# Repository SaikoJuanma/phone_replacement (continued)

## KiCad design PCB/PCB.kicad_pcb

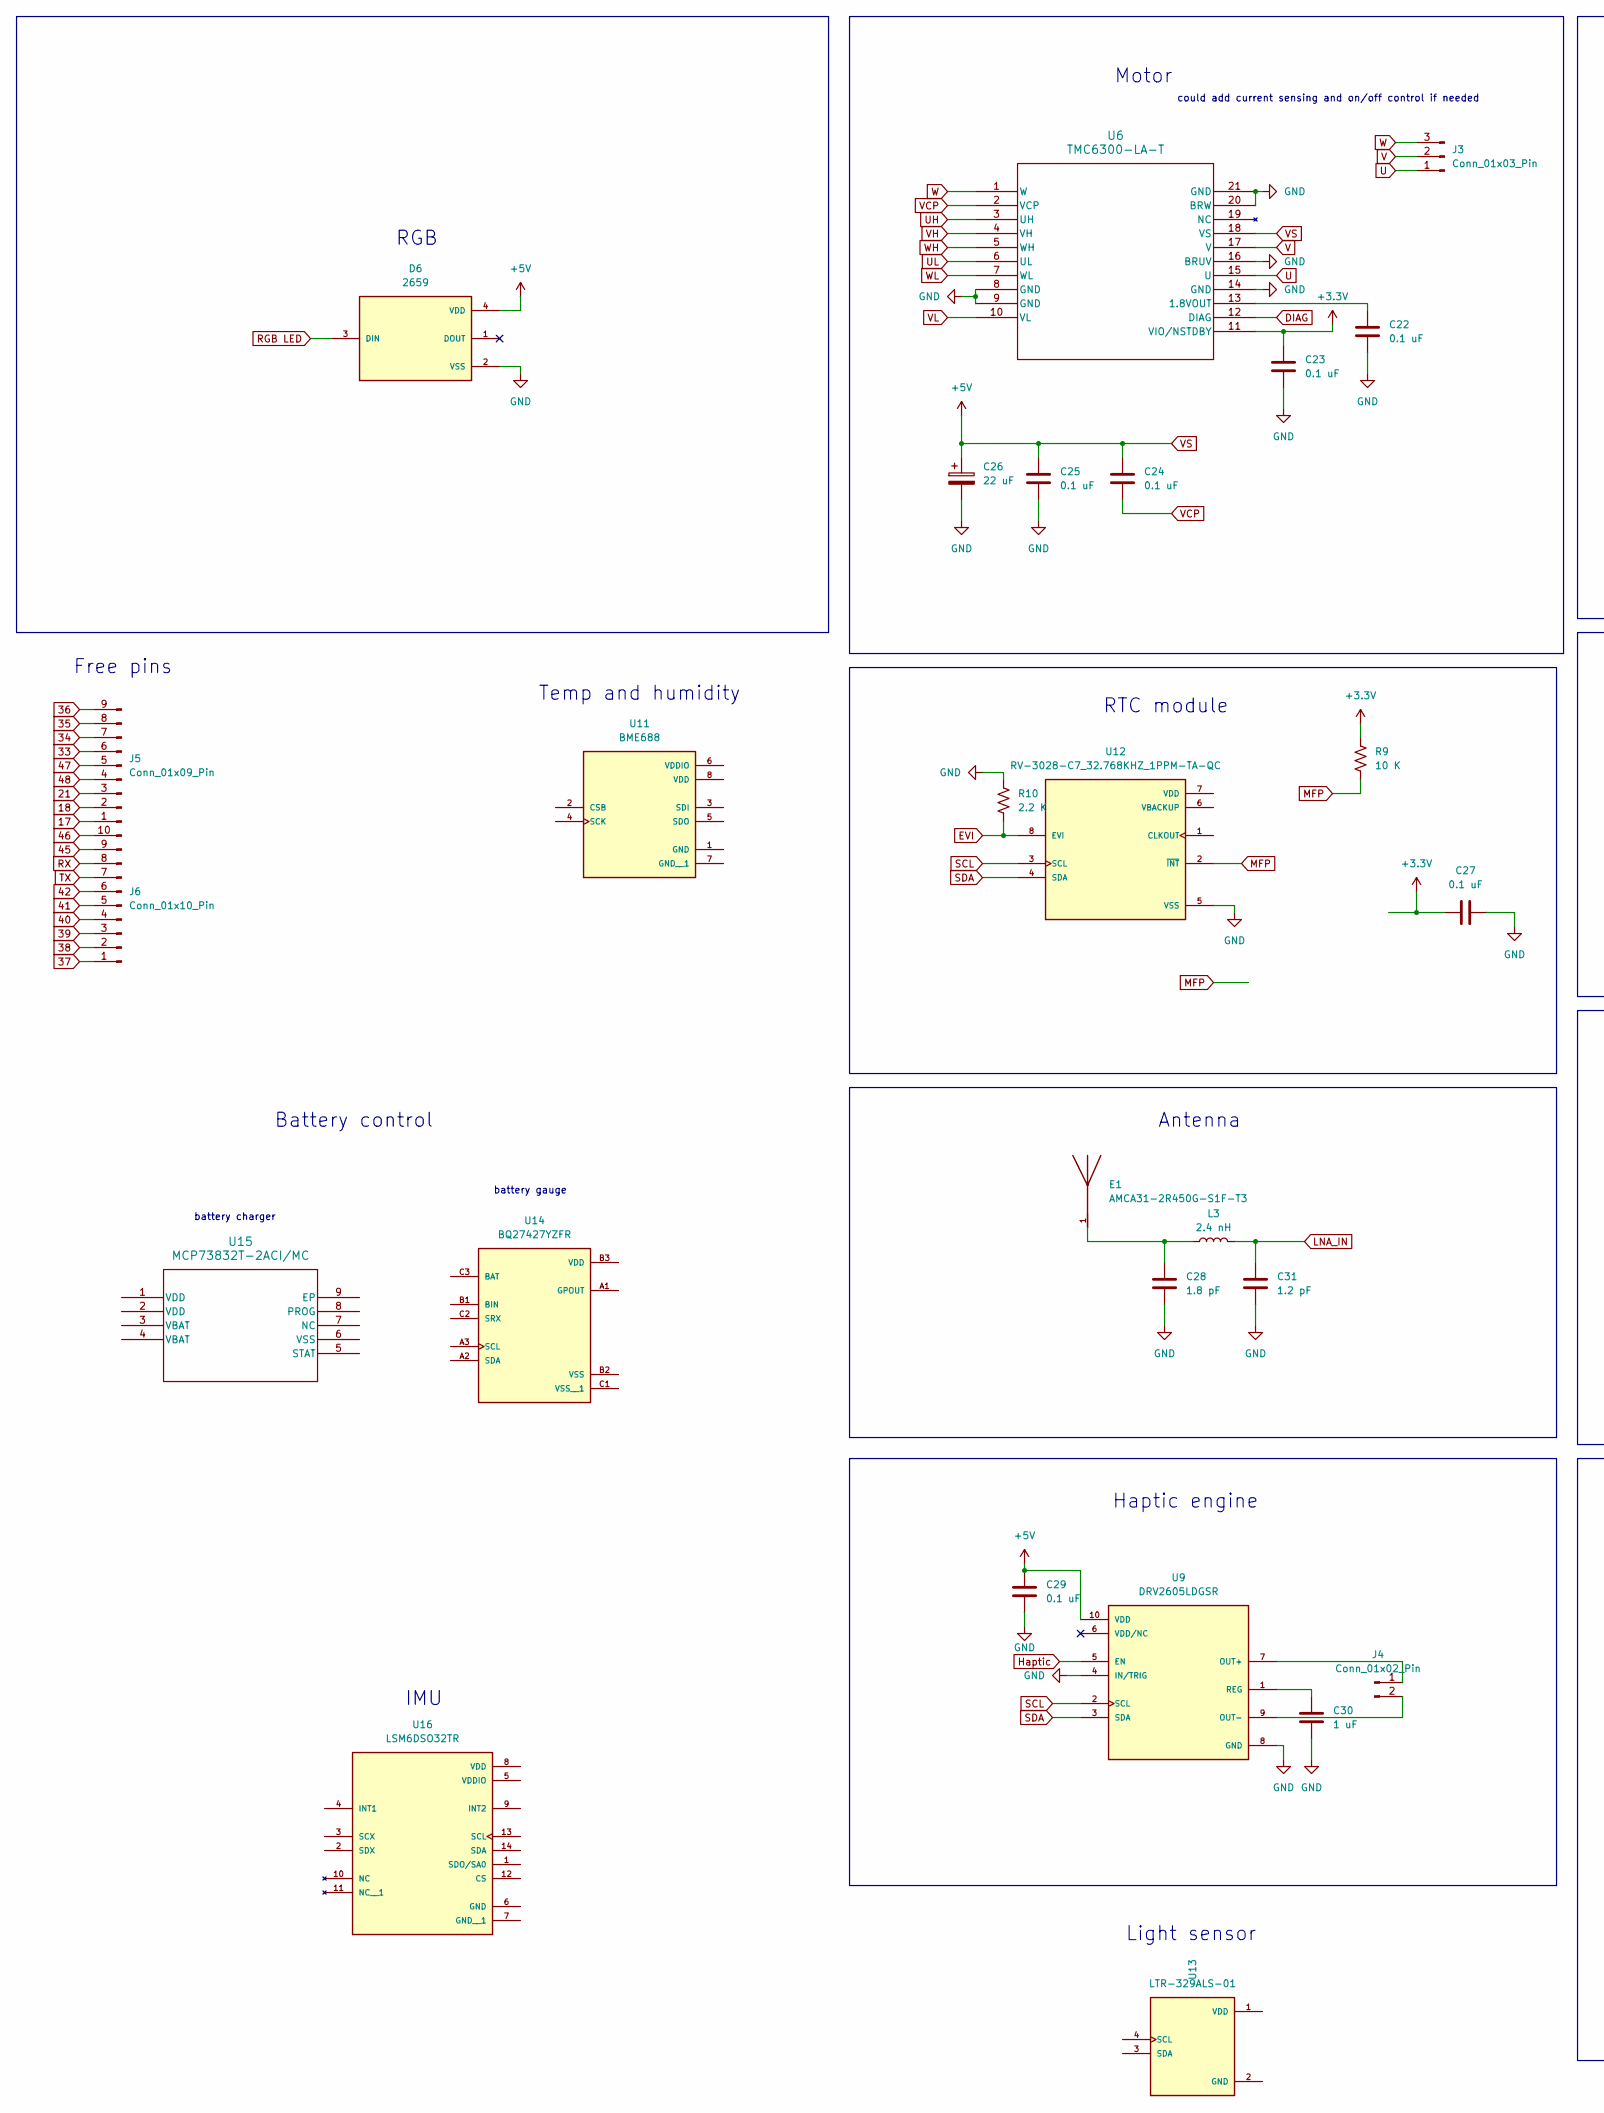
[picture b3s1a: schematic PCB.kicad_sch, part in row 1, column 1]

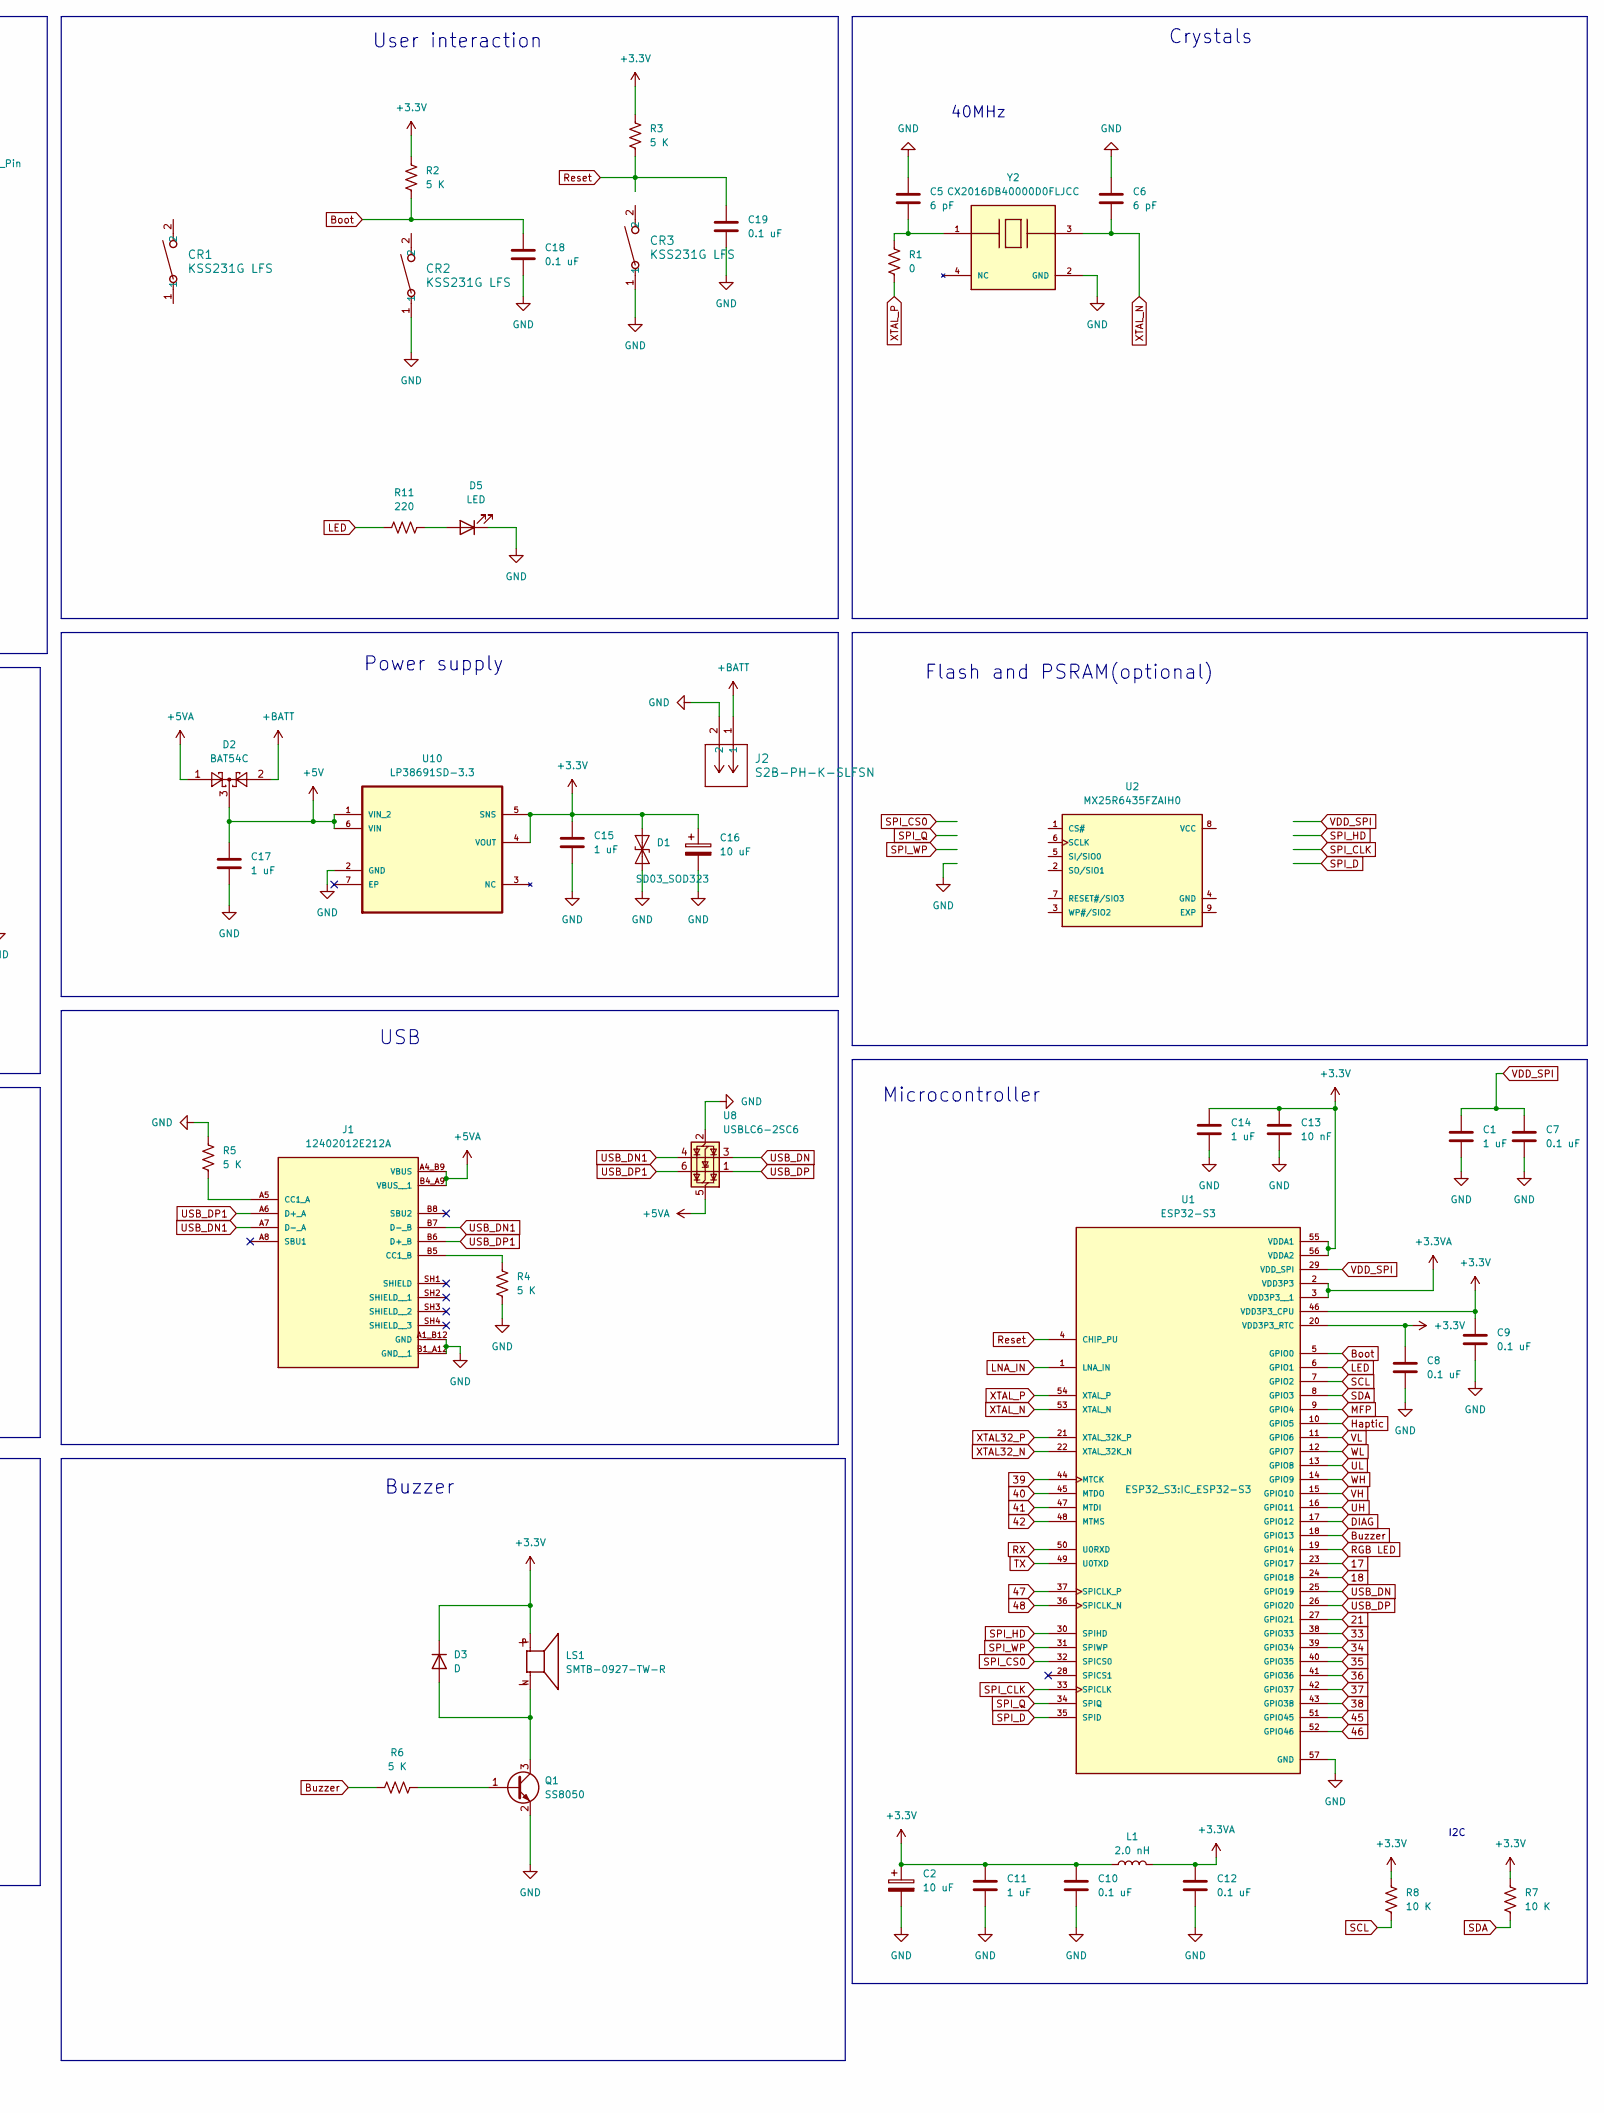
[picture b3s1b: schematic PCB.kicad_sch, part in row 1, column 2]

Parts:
C1, C11, C14, C15, C17, C30: 1 uF; C_0201_0603Metric_Pad0.64x0.40mm_HandSolder
C2, C16: 10 uF; CP_EIA-1608-08_AVX-J_HandSolder
C5, C6: 6 pF; C_0201_0603Metric_Pad0.64x0.40mm_HandSolder
C7, C8, C9, C10, C12, C18, C19, C22, C23, C24, C25, C27, C29: 0.1 uF; C_0201_0603Metric_Pad0.64x0.40mm_HandSolder
C13: 10 nF; C_0201_0603Metric_Pad0.64x0.40mm_HandSolder
C26: 22 uF; CP_EIA-1608-08_AVX-J_HandSolder
C28: 1.8 pF; C_0201_0603Metric
C31: 1.2 pF; C_0201_0603Metric
CR1, CR2, CR3: KSS231G LFS; SW_KSS2
D1: SD03_SOD323; D_SOD-323
D2: BAT54C; SOT-23
D3: D
D5: LED; LED_0805_2012Metric
D6: 2659; PARTREV 01
E1: AMCA31-2R450G-S1F-T3; XDCR_AMCA31-2R450G-S1F-T3; PARTREV 03-21-19
J1: 12402012E212A; AMPHENOL_12402012E212A; PARTREV 4
J2: S2B-PH-K-SLFSN; JST_ZH_B2B-ZR_1x02_P1.50mm_Vertical
J3: Conn_01x03_Pin; JST_ZH_B3B-ZR_1x03_P1.50mm_Vertical
J4: Conn_01x02_Pin; JST_ZH_B2B-ZR_1x02_P1.50mm_Vertical
J5: Conn_01x09_Pin; PinHeader_1x09_P1.27mm_Vertical
J6: Conn_01x10_Pin; PinHeader_1x10_P1.27mm_Vertical
L1: 2.0 nH; L_0201_0603Metric_Pad0.64x0.40mm_HandSolder
L3: 2.4 nH; L_0201_0603Metric
LS1: SMTB-0927-TW-R; XDCR_SMTB-0927-TW-R; PARTREV 6/1/17
Q1: SS8050; SOT-23
R1: 0; R_0201_0603Metric_Pad0.64x0.40mm_HandSolder
R2, R3, R4, R5, R6: 5 K; R_0201_0603Metric_Pad0.64x0.40mm_HandSolder
R7, R8, R9: 10 K; R_0201_0603Metric_Pad0.64x0.40mm_HandSolder
R10: 2.2 K; R_0201_0603Metric_Pad0.64x0.40mm_HandSolder
R11: 220; R_0201_0603Metric_Pad0.64x0.40mm_HandSolder
U1: ESP32-S3; IC_ESP32-S3; PARTREV v1.2
U2: MX25R6435FZAIH0; SON80P400X400X60-9N
U6: TMC6300-LA-T; 21-100586_K2033&plus_1C_ADI-M; MPN 175-TMC6300-LA-TCT-ND
U8: USBLC6-2SC6; SOT-23-6
U9: DRV2605LDGSR; SOP50P490X110-10N; PARTREV D
U10: LP38691SD-3.3; DFN300X300X80-7N; MPN LP38691SD-3.3
U11: BME688; IC_BME688; PARTREV 1.0
U12: RV-3028-C7_32.768KHZ_1PPM-TA-QC; MicroCrystal_C7_SON-8_1.5x3.2mm_P0.9mm; PARTREV 1.3
U13: LTR-329ALS-01; IC_LTR-329ALS-01; PARTREV 1.8
U14: BQ27427YZFR; IC_BQ27427YZFR; PARTREV December 2022
U15: MCP73832T-2ACI/MC; DFN8_2x3MC_MCH-L
U16: LSM6DSO32TR; XDCR_LSM6DSO32TR; PARTREV 1
Y2: CX2016DB40000D0FLJCC; OSC_CX2016DB40000D0FLJCC; PARTREV October 2024

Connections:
17: J5.1, U1.23 (GPIO17)
18: J5.2, U1.24 (GPIO18)
21: J5.3, U1.27 (GPIO21)
33: J5.6, U1.38 (GPIO33)
34: J5.7, U1.39 (GPIO34)
35: J5.8, U1.40 (GPIO35)
36: J5.9, U1.41 (GPIO36)
37: J6.1, U1.42 (GPIO37)
38: J6.2, U1.43 (GPIO38)
39: J6.3, U1.44 (MTCK)
40: J6.4, U1.45 (MTDO)
41: J6.5, U1.47 (MTDI)
42: J6.6, U1.48 (MTMS)
45: J6.9, U1.51 (GPIO45)
46: J6.10, U1.52 (GPIO46)
47: J5.5, U1.37 (SPICLK_P)
48: J5.4, U1.36 (SPICLK_N)
+3.3V: C2.1, C8.1, C9.1, C10.1, C11.1, C13.1, C14.1, C15.1, C16.1, C23.1, C27.1, D1.2 (A2), D3.1 (K), L1.1, LS1.P, R2.1, R3.1, R7.2, R8.2, R9.2, U1.20 (VDD3P3_RTC), U1.46 (VDD3P3_CPU), U1.55 (VDDA1), U1.56 (VDDA2), U6.11 (VIO/NSTDBY), U10.4 (VOUT), U10.5 (SNS)
+3.3VA: C12.1, L1.2, U1.2 (VDD3P3), U1.3 (VDD3P3__1)
+5VA: D2.1, J1.A4_B9 (VBUS), J1.B4_A9 (VBUS__1), U8.5 (VBUS)
+BATT: D2.2, J2.1
Boot: C18.1, R2.2, U1.5 (GPIO0)
Buzzer: R6.2, U1.18 (GPIO13)
DIAG: U1.17 (GPIO12), U6.12 (DIAG)
EVI: R10.2, U12.8 (EVI)
GND: C1.2, C2.2, C5.1, C6.1, C7.2, C8.2, C9.2, C10.2, C11.2, C12.2, C13.2, C14.2, C15.2, C16.2, C17.2, C18.2, C19.2, C22.2, C23.2, C25.2, C26.2, C27.2, C28.1, C29.2, C30.2, C31.1, CR2.1, CR3.1, D1.1 (A1), D5.1 (K), D6.2 (VSS), J1.A1_B12 (GND), J1.B1_A12 (GND__1), J2.2, Q1.2 (E), R4.2, R5.1, R10.1, U1.57 (GND), U6.8 (GND), U6.9 (GND), U6.14 (GND), U6.16 (BRUV), U6.20 (BRW), U6.21 (GND), U8.2 (GND), U9.4 (IN/TRIG), U9.8 (GND), U10.2 (GND), U12.5 (VSS), Y2.2 (GND)
Haptic: U1.10 (GPIO5), U9.5 (EN)
LED: R11.1, U1.6 (GPIO1)
LNA_IN: C31.2, L3.2, U1.1 (LNA_IN)
MFP: R9.1, U1.9 (GPIO4), U12.2 (~INT)
unnamed: C5.2, R1.1, Y2.1
unnamed: C28.2, E1.1, L3.1
unnamed: D3.2 (A), LS1.N, Q1.3 (C)
unnamed: D5.2 (A), R11.2
unnamed: J1.A5 (CC1_A), R5.2
unnamed: J1.B5 (CC1_B), R4.1
unnamed: J4.1, U9.7 (OUT+)
unnamed: J4.2, U9.9 (OUT-)
unnamed: Q1.1 (B), R6.1
unnamed: C22.1, U6.13 (1.8VOUT)
unnamed: C30.1, U9.1 (REG)
RGB LED: D6.3 (DIN), U1.19 (GPIO14)
RX: J6.8, U1.50 (U0RXD)
Reset: C19.1, R3.2, U1.4 (CHIP_PU)
SCL: R8.1, U1.7 (GPIO2), U9.2 (SCL), U12.3 (SCL)
SDA: R7.1, U1.8 (GPIO3), U9.3 (SDA), U12.4 (SDA)
SPI_CLK: U1.33 (SPICLK)
SPI_CS0: U1.32 (SPICS0)
SPI_D: U1.35 (SPID)
SPI_HD: U1.30 (SPIHD)
SPI_Q: U1.34 (SPIQ)
SPI_WP: U1.31 (SPIWP)
TX: J6.7, U1.49 (U0TXD)
U: J3.1, U6.15 (U)
UH: U1.16 (GPIO11), U6.3 (UH)
UL: U1.13 (GPIO8), U6.6 (UL)
USB_DN: U1.25 (GPIO19), U8.3 (I/O2)
USB_DN1: J1.A7 (D-_A), J1.B7 (D-_B), U8.4 (I/O2)
USB_DP: U1.26 (GPIO20), U8.1 (I/O1)
USB_DP1: J1.A6 (D+_A), J1.B6 (D+_B), U8.6 (I/O1)
V: J3.2, U6.17 (V)
VCP: C24.2, U6.2 (VCP)
VDD_SPI: C1.1, C7.1, U1.29 (VDD_SPI)
VH: U1.15 (GPIO10), U6.4 (VH)
VL: U1.11 (GPIO6), U6.10 (VL)
VS: C17.1, C24.1, C25.1, C26.1, C29.1, D2.3, D6.4 (VDD), U6.18 (VS), U9.10 (VDD), U10.1 (VIN_2), U10.6 (VIN)
W: J3.3, U6.1 (W)
WH: U1.14 (GPIO9), U6.5 (WH)
WL: U1.12 (GPIO7), U6.7 (WL)
XTAL32_N: U1.22 (XTAL_32K_N)
XTAL32_P: U1.21 (XTAL_32K_P)
XTAL_N: C6.2, U1.53 (XTAL_N), Y2.3
XTAL_P: R1.2, U1.54 (XTAL_P)

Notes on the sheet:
Antenna
Crystals
Motor
Free pins
Flash and PSRAM(optional)
could add current sensing and on/off control if needed
Microcontroller
40MHz
Power supply
I2C
Temp and humidity
IMU
Haptic engine
Battery control
Light sensor
User interaction
RGB
battery gauge
battery charger
USB
RTC module
Buzzer

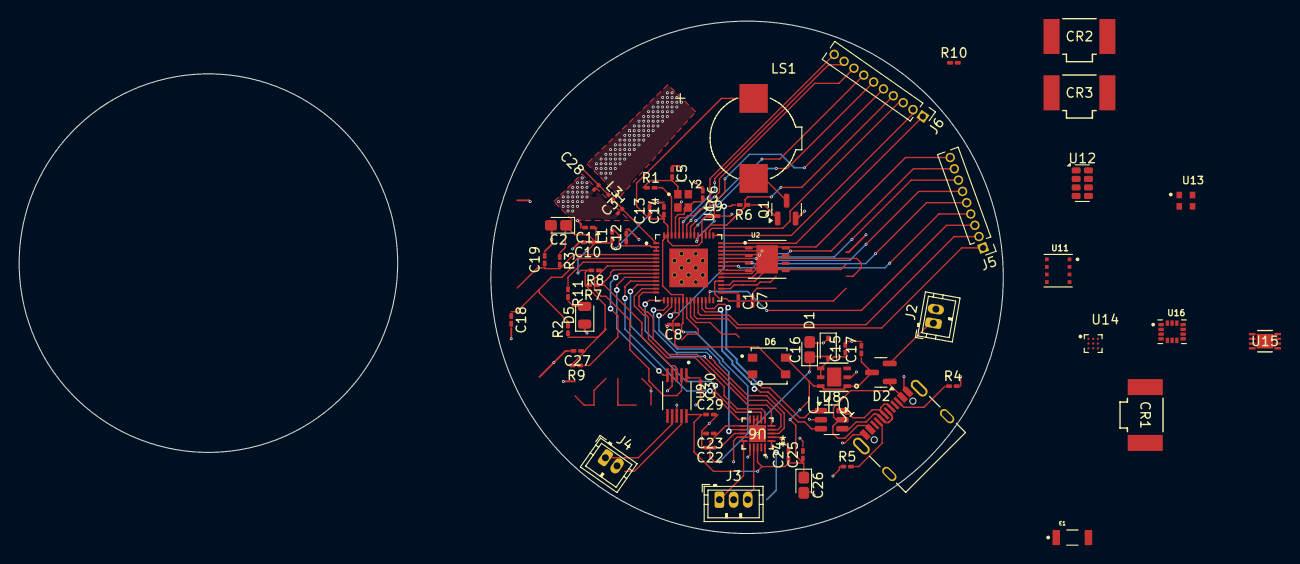
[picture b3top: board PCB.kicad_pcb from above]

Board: 2 copper layers, 54.1 x 54.1 mm, 69 parts (0 on the bottom side), 65 nets.

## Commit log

2025-08-17 hello world compiles and works
2025-08-24 PCB files added, first version not ready
2025-08-25 schematic almost ready
2025-08-26 more pcb changes, schematic ready, now footprint
2025-08-27 first vesrion of pcb ready
2025-08-27 to do updated
2025-08-27 git ignore modified
2025-08-29 last changes for the pcb
2025-08-31 new pcb added
2025-09-01 finally git ignore corected
2025-09-15 re organization of top and bottom pcb
2025-09-21 TOP-PCB ready
2025-09-21 start routing on bottom pcb
2025-09-22 connections for bottom pcb
2025-09-24 things to improve
2025-09-27 I think its ready again
2025-09-28 starting to add MPN
